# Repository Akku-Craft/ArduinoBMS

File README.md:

# Akku-Craft Module Firmware

Firmware for the Akku-Craft hardware platform.

This repository contains the source code for the battery management and monitoring firmware.

**Work in Progress**  
This firmware is currently under active development. APIs, features, and structure are subject to change. It is not yet production-ready.

## Scope
This repo focuses on:
- Embedded firmware for the Akku-Craft module
- Battery management logic
- Monitoring, communication, and safety functions
- Build system and configuration

Hardware design files, web interface, and mechanical assets are maintained in separate repositories.

## Old Firmware
The old version is available here:  
[https://github.com/Akku-Craft/ArduinoBMS-old](https://github.com/Akku-Craft/ArduinoBMS-old)

## Requirements
- PlatformIO (recommended) or Arduino IDE
- Compatible toolchain for the target microcontroller
- Git for version control

## Quick Start
1. Clone this repository.
2. Open the project in PlatformIO (or your preferred IDE).
3. Build and flash the firmware to the target hardware.
4. Work from the project root (do not move files out of this directory).

## Repository Structure
```text
src/                  # Main source code
include/              # Header files
lib/                  # External libraries and dependencies
test/                 # Unit and integration tests
platformio.ini        # PlatformIO project configuration
README.md
LICENSE               # Will be added later

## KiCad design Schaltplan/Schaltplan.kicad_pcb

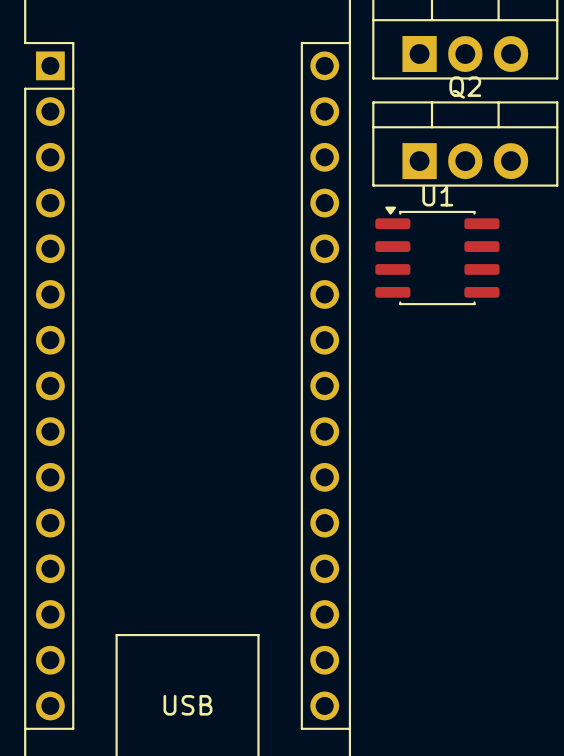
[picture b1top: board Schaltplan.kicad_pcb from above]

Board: 2 copper layers, 4 parts (0 on the bottom side), 6 nets, no tracks yet.

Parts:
A1: Arduino_Nano
Q1, Q2: IRLZ44N; TO-220-3_Vertical
U1: ACS712xLCTR-05B; SOIC-8_3.9x4.9mm_P1.27mm

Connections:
unnamed: A1.27 (+5V), U1.8 (VCC)
unnamed: A1.26 (A7), U1.7 (VIOUT)
unnamed: A1.4 (GND), A1.5 (D2), Q1.2 (D), Q2.2 (D), U1.5 (GND)
unnamed: Q1.3 (S), Q2.3 (S)
unnamed: U1.3 (IP-), U1.4 (IP-)
unnamed: U1.1 (IP+), U1.2 (IP+)

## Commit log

2026-02-11 Zwischenspeichern vor Sync
2026-02-14 Plan changes
2026-02-14 Add ACS712 current sensor and update schematic layout
2026-02-14 Moved Schaltplan
2026-06-27 Create README.md for Akku-Craft firmware project
    Added initial README.md with project details and requirements.
